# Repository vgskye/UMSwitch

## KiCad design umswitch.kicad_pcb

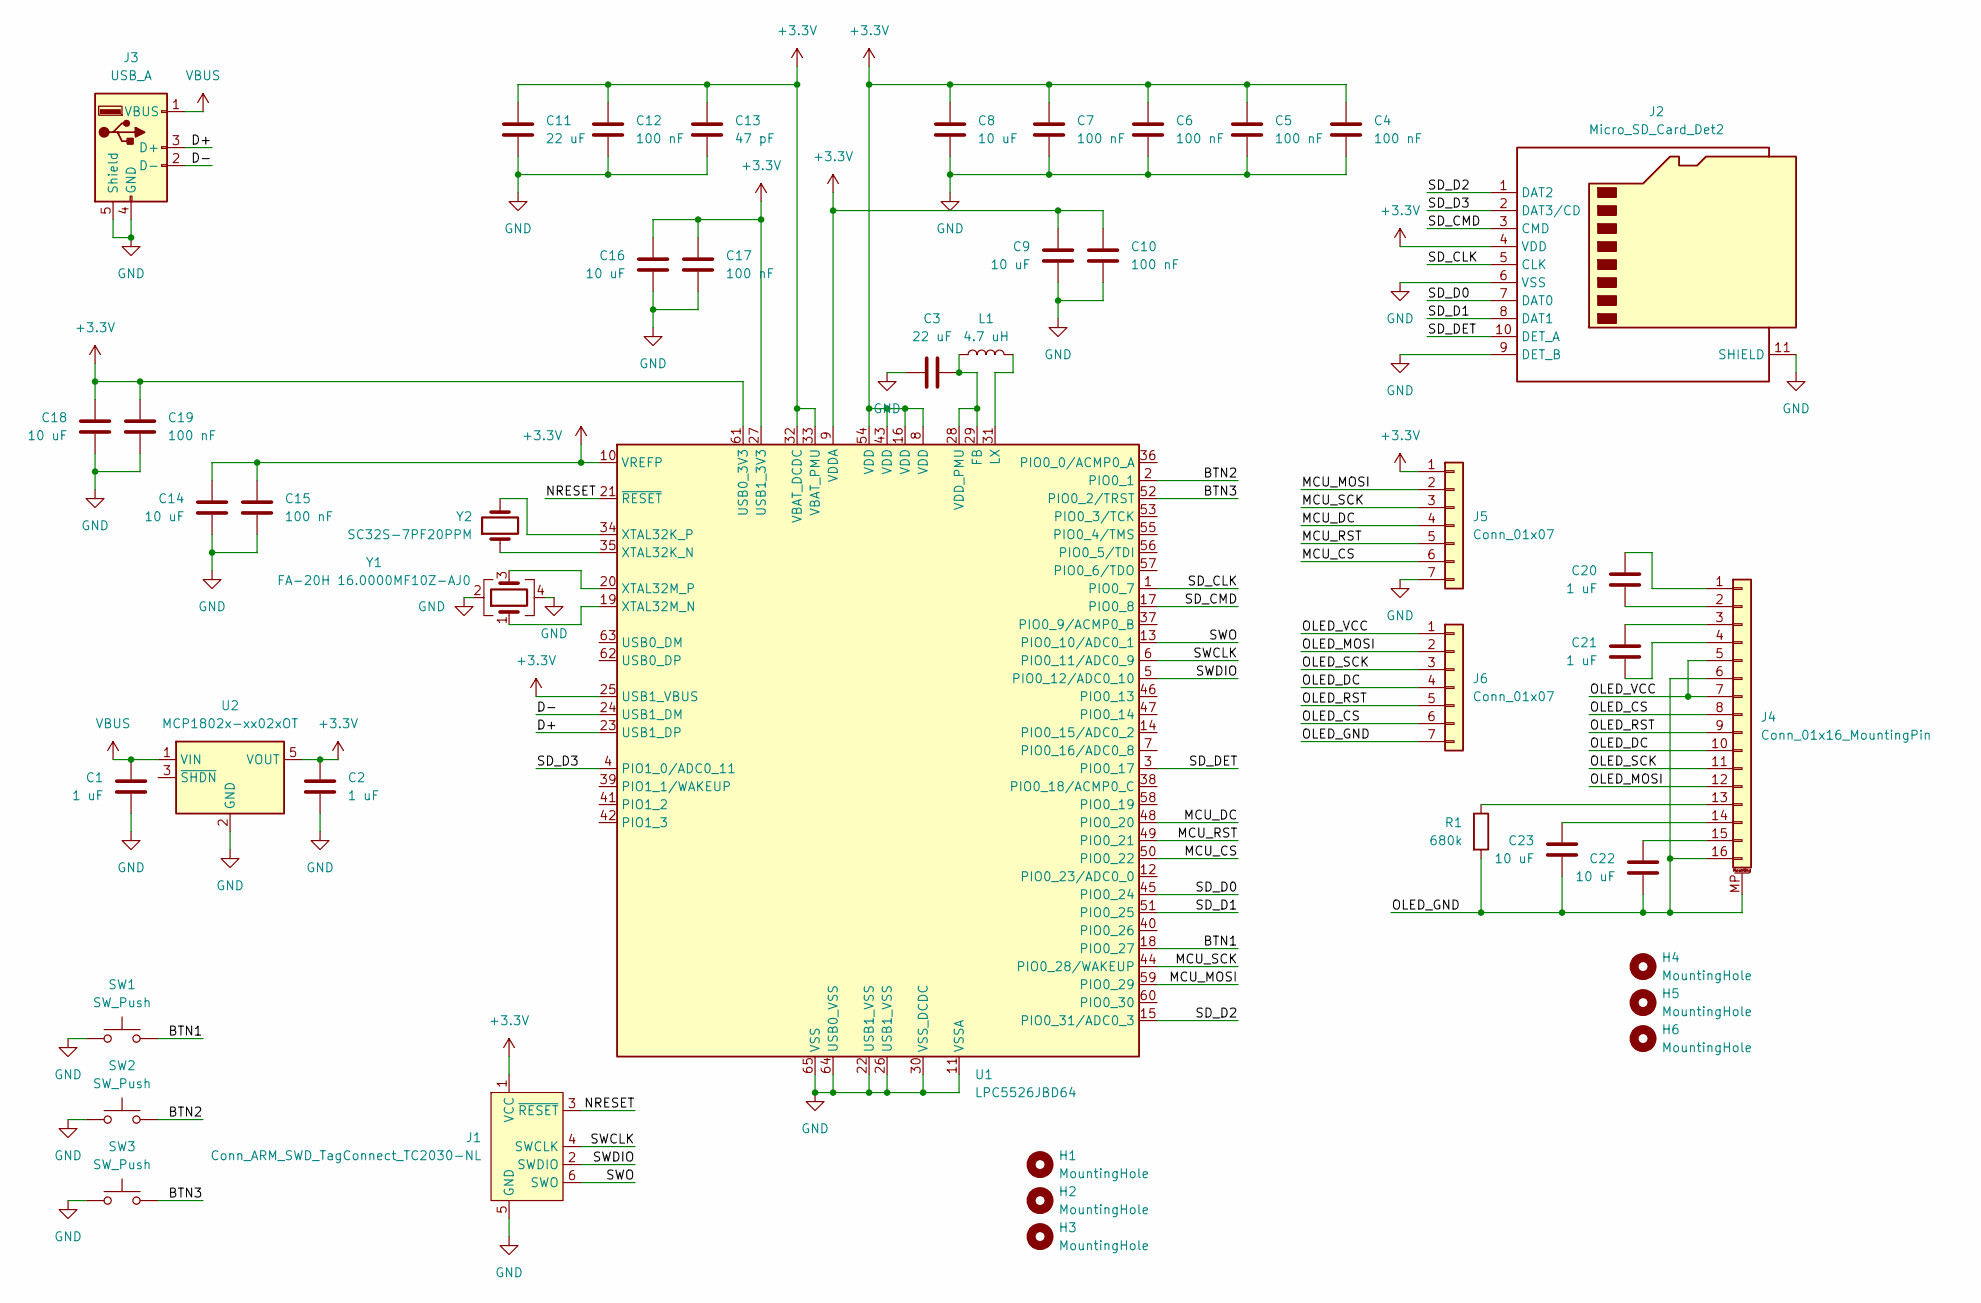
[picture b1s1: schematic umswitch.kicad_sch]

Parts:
C1, C2, C20, C21: 1 uF; C_0603_1608Metric
C3, C11: 22 uF; C_0603_1608Metric
C4, C5, C6, C7, C10, C12, C15, C17, C19: 100 nF; C_0603_1608Metric
C8, C9, C14, C16, C18, C22, C23: 10 uF; C_0603_1608Metric
C13: 47 pF; C_0603_1608Metric
H1, H2, H3, H4, H5, H6: MountingHole; MountingHole_2.2mm_M2_ISO14580
J1: Conn_ARM_SWD_TagConnect_TC2030-NL; Tag-Connect_TC2030-IDC-NL_2x03_P1.27mm_Vertical
J2: Micro_SD_Card_Det2; microSD_HC_Hirose_DM3D-SF
J3: USB_A; USB_A_CNCTech_1001-011-01101_Horizontal
J4: Conn_01x16_MountingPin; Hirose_FH12-16S-0.5SH_1x16-1MP_P0.50mm_Horizontal
J5: Conn_01x07; PinHeader_1x07_P2.54mm_Vertical
J6: Conn_01x07; PinSocket_1x07_P2.54mm_Vertical
L1: 4.7 uH; L_0603_1608Metric
R1: 680k; R_0603_1608Metric
SW1, SW2, SW3: SW_Push; SW_SPST_B3U-3000P
U1: LPC5526JBD64; HTQFP-64-1EP_10x10mm_P0.5mm_EP4x4mm
U2: MCP1802x-xx02xOT; SOT-23-5
Y1: FA-20H 16.0000MF10Z-AJ0; Crystal_SMD_2520-4Pin_2.5x2.0mm
Y2: SC32S-7PF20PPM; Crystal_SMD_3215-2Pin_3.2x1.5mm

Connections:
+3.3V: C2.1, C4.2, C5.2, C6.2, C7.2, C8.2, C9.2, C10.2, C11.2, C12.2, C13.2, C14.2, C15.2, C16.2, C17.2, C18.2, C19.2, J1.1 (VCC), J2.4 (VDD), J5.1, U1.8 (VDD), U1.9 (VDDA), U1.10 (VREFP), U1.16 (VDD), U1.25 (USB1_VBUS), U1.27 (USB1_3V3), U1.32 (VBAT_DCDC), U1.33 (VBAT_PMU), U1.43 (VDD), U1.54 (VDD), U1.61 (USB0_3V3), U2.5 (VOUT)
/BTN1: SW1.2, U1.18 (PIO0_27)
/BTN2: SW2.2, U1.2 (PIO0_1)
/BTN3: SW3.2, U1.52 (PIO0_2/TRST)
/D+: J3.3 (D+), U1.23 (USB1_DP)
/D-: J3.2 (D-), U1.24 (USB1_DM)
/MCU_CS: J5.6, U1.50 (PIO0_22)
/MCU_DC: J5.4, U1.48 (PIO0_20)
/MCU_MOSI: J5.2, U1.59 (PIO0_29)
/MCU_RST: J5.5, U1.49 (PIO0_21)
/MCU_SCK: J5.3, U1.44 (PIO0_28/WAKEUP)
/NRESET: J1.3 (~RESET), U1.21 (~RESET)
/OLED_CS: J4.8, J6.6
/OLED_DC: J4.10, J6.4
/OLED_GND: C22.1, C23.1, J4.6, J4.16, J4.MP (MountPin), J6.7, R1.2
/OLED_MOSI: J4.12, J6.2
/OLED_RST: J4.9, J6.5
/OLED_SCK: J4.11, J6.3
/OLED_VCC: J4.5, J4.7, J6.1
/SD_CLK: J2.5 (CLK), U1.1 (PIO0_7)
/SD_CMD: J2.3 (CMD), U1.17 (PIO0_8)
/SD_D0: J2.7 (DAT0), U1.45 (PIO0_24)
/SD_D1: J2.8 (DAT1), U1.51 (PIO0_25)
/SD_D2: J2.1 (DAT2), U1.15 (PIO0_31/ADC0_3)
/SD_D3: J2.2 (DAT3/CD), U1.4 (PIO1_0/ADC0_11)
/SD_DET: J2.10 (DET_A), U1.3 (PIO0_17)
/SWCLK: J1.4 (SWCLK), U1.6 (PIO0_11/ADC0_9)
/SWDIO: J1.2 (SWDIO), U1.5 (PIO0_12/ADC0_10)
/SWO: J1.6 (SWO), U1.13 (PIO0_10/ADC0_1)
GND: C1.2, C2.2, C3.1, C4.1, C5.1, C6.1, C7.1, C8.1, C9.1, C10.1, C11.1, C12.1, C13.1, C14.1, C15.1, C16.1, C17.1, C18.1, C19.1, J1.5 (GND), J2.6 (VSS), J2.9 (DET_B), J2.11 (SHIELD), J3.4 (GND), J3.5 (Shield), J5.7, SW1.1, SW2.1, SW3.1, U1.11 (VSSA), U1.22 (USB1_VSS), U1.26 (USB1_VSS), U1.30 (VSS_DCDC), U1.64 (USB0_VSS), U1.65 (VSS), U2.2 (GND), Y1.2, Y1.4
unnamed: C20.2, J4.1
unnamed: C20.1, J4.2
unnamed: C21.2, J4.3
unnamed: C21.1, J4.4
unnamed: J4.13, R1.1
unnamed: C23.2, J4.14
unnamed: C22.2, J4.15
unnamed: C3.2, L1.1, U1.28 (VDD_PMU), U1.29 (FB)
unnamed: L1.2, U1.31 (LX)
unnamed: U1.35 (XTAL32K_N), Y2.1
unnamed: U1.34 (XTAL32K_P), Y2.2
unnamed: U1.19 (XTAL32M_N), Y1.1
unnamed: U1.20 (XTAL32M_P), Y1.3
VBUS: C1.1, J3.1 (VBUS), U2.1 (VIN)

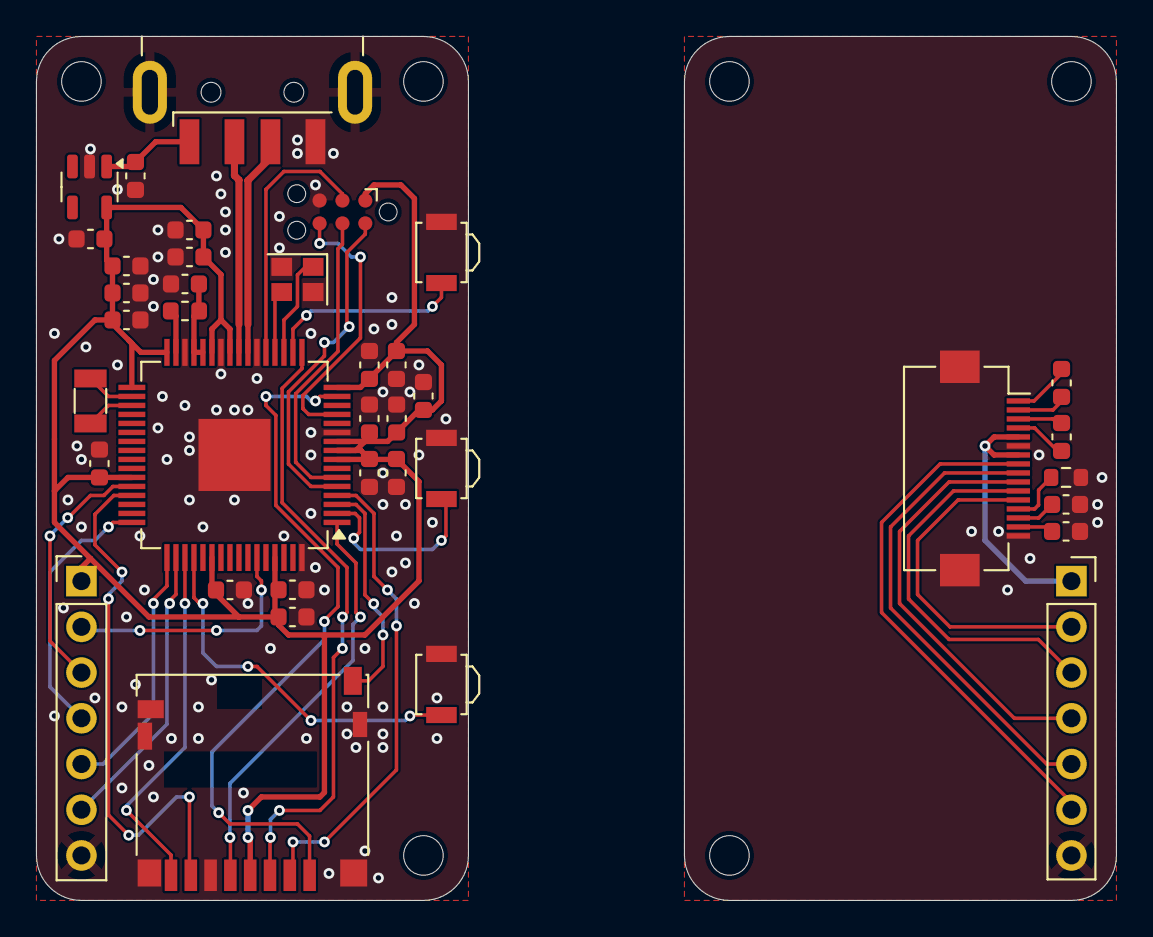
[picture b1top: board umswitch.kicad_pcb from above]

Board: 2 copper layers, 60.0 x 48.0 mm, 44 parts (0 on the bottom side), 44 nets.

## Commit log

2025-10-06 draft 1
2025-10-06 fix some drc issues
